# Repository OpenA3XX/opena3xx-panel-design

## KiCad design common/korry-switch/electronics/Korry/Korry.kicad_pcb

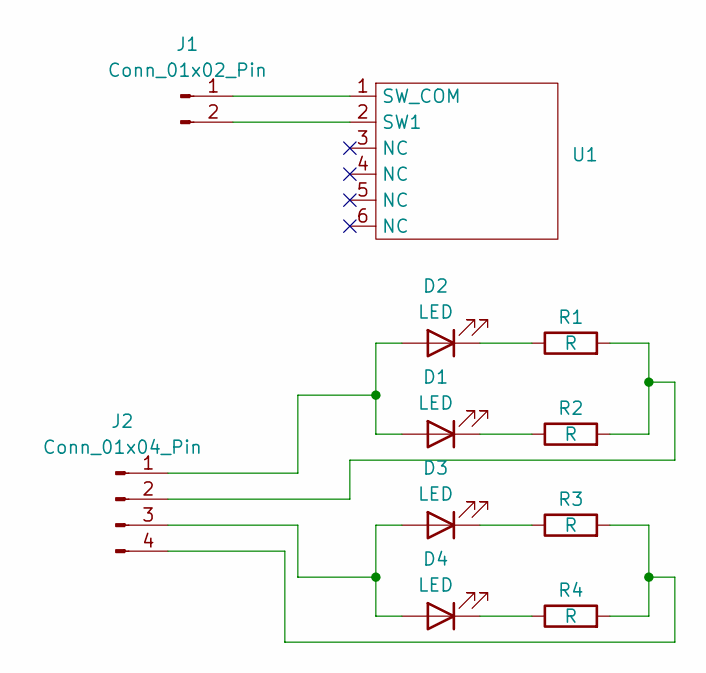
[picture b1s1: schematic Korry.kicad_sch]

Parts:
D1, D2, D3, D4: LED; LED_D3.0mm
J1: Conn_01x02_Pin; PinHeader_1x02_P2.54mm_Vertical
J2: Conn_01x04_Pin; PinHeader_1x04_P2.54mm_Vertical
R1, R2, R3, R4: R; R_1210_3225Metric_Pad1.30x2.65mm_HandSolder
U1: Korry_Switch_Discrete

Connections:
unnamed: D1.2 (A), D2.2 (A), J2.1
unnamed: D1.1 (K), R2.1
unnamed: D2.1 (K), R1.1
unnamed: D3.2 (A), D4.2 (A), J2.3
unnamed: D3.1 (K), R3.1
unnamed: D4.1 (K), R4.1
unnamed: J1.1, U1.1 (SW_COM)
unnamed: J1.2, U1.2 (SW1)
unnamed: J2.2, R1.2, R2.2
unnamed: J2.4, R3.2, R4.2

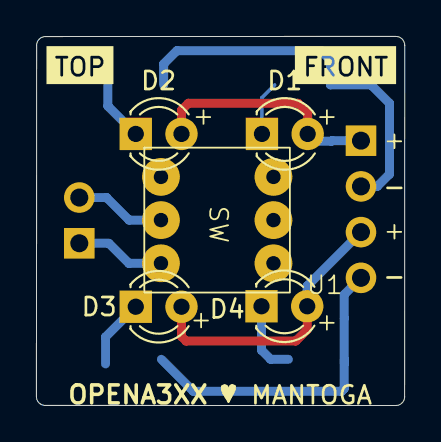
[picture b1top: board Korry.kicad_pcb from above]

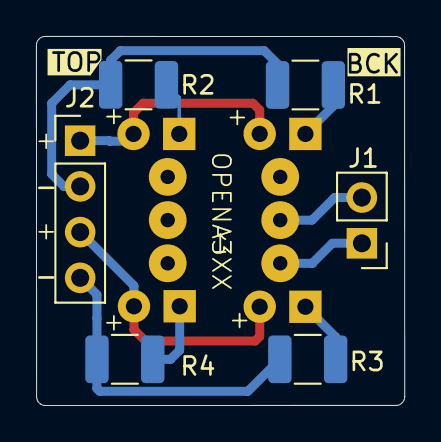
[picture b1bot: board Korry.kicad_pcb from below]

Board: 2 copper layers, 20.5 x 20.5 mm, 11 parts (6 on the bottom side), 10 nets.

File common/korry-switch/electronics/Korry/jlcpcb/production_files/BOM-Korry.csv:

Comment,Designator,Footprint,LCSC,Quantity
R,"R1,R2,R3,R4",R_1210_3225Metric_Pad1.30x2.65mm_HandSolder,C105021,4
LED,D2,LED_D3.0mm,,1
LED,D1,LED_D3.0mm,,1
Conn_01x04_Pin,J2,PinHeader_1x04_P2.54mm_Vertical,,1
LED,D4,LED_D3.0mm,,1
Conn_01x02_Pin,J1,PinHeader_1x02_P2.54mm_Vertical,,1
LED,D3,LED_D3.0mm,,1

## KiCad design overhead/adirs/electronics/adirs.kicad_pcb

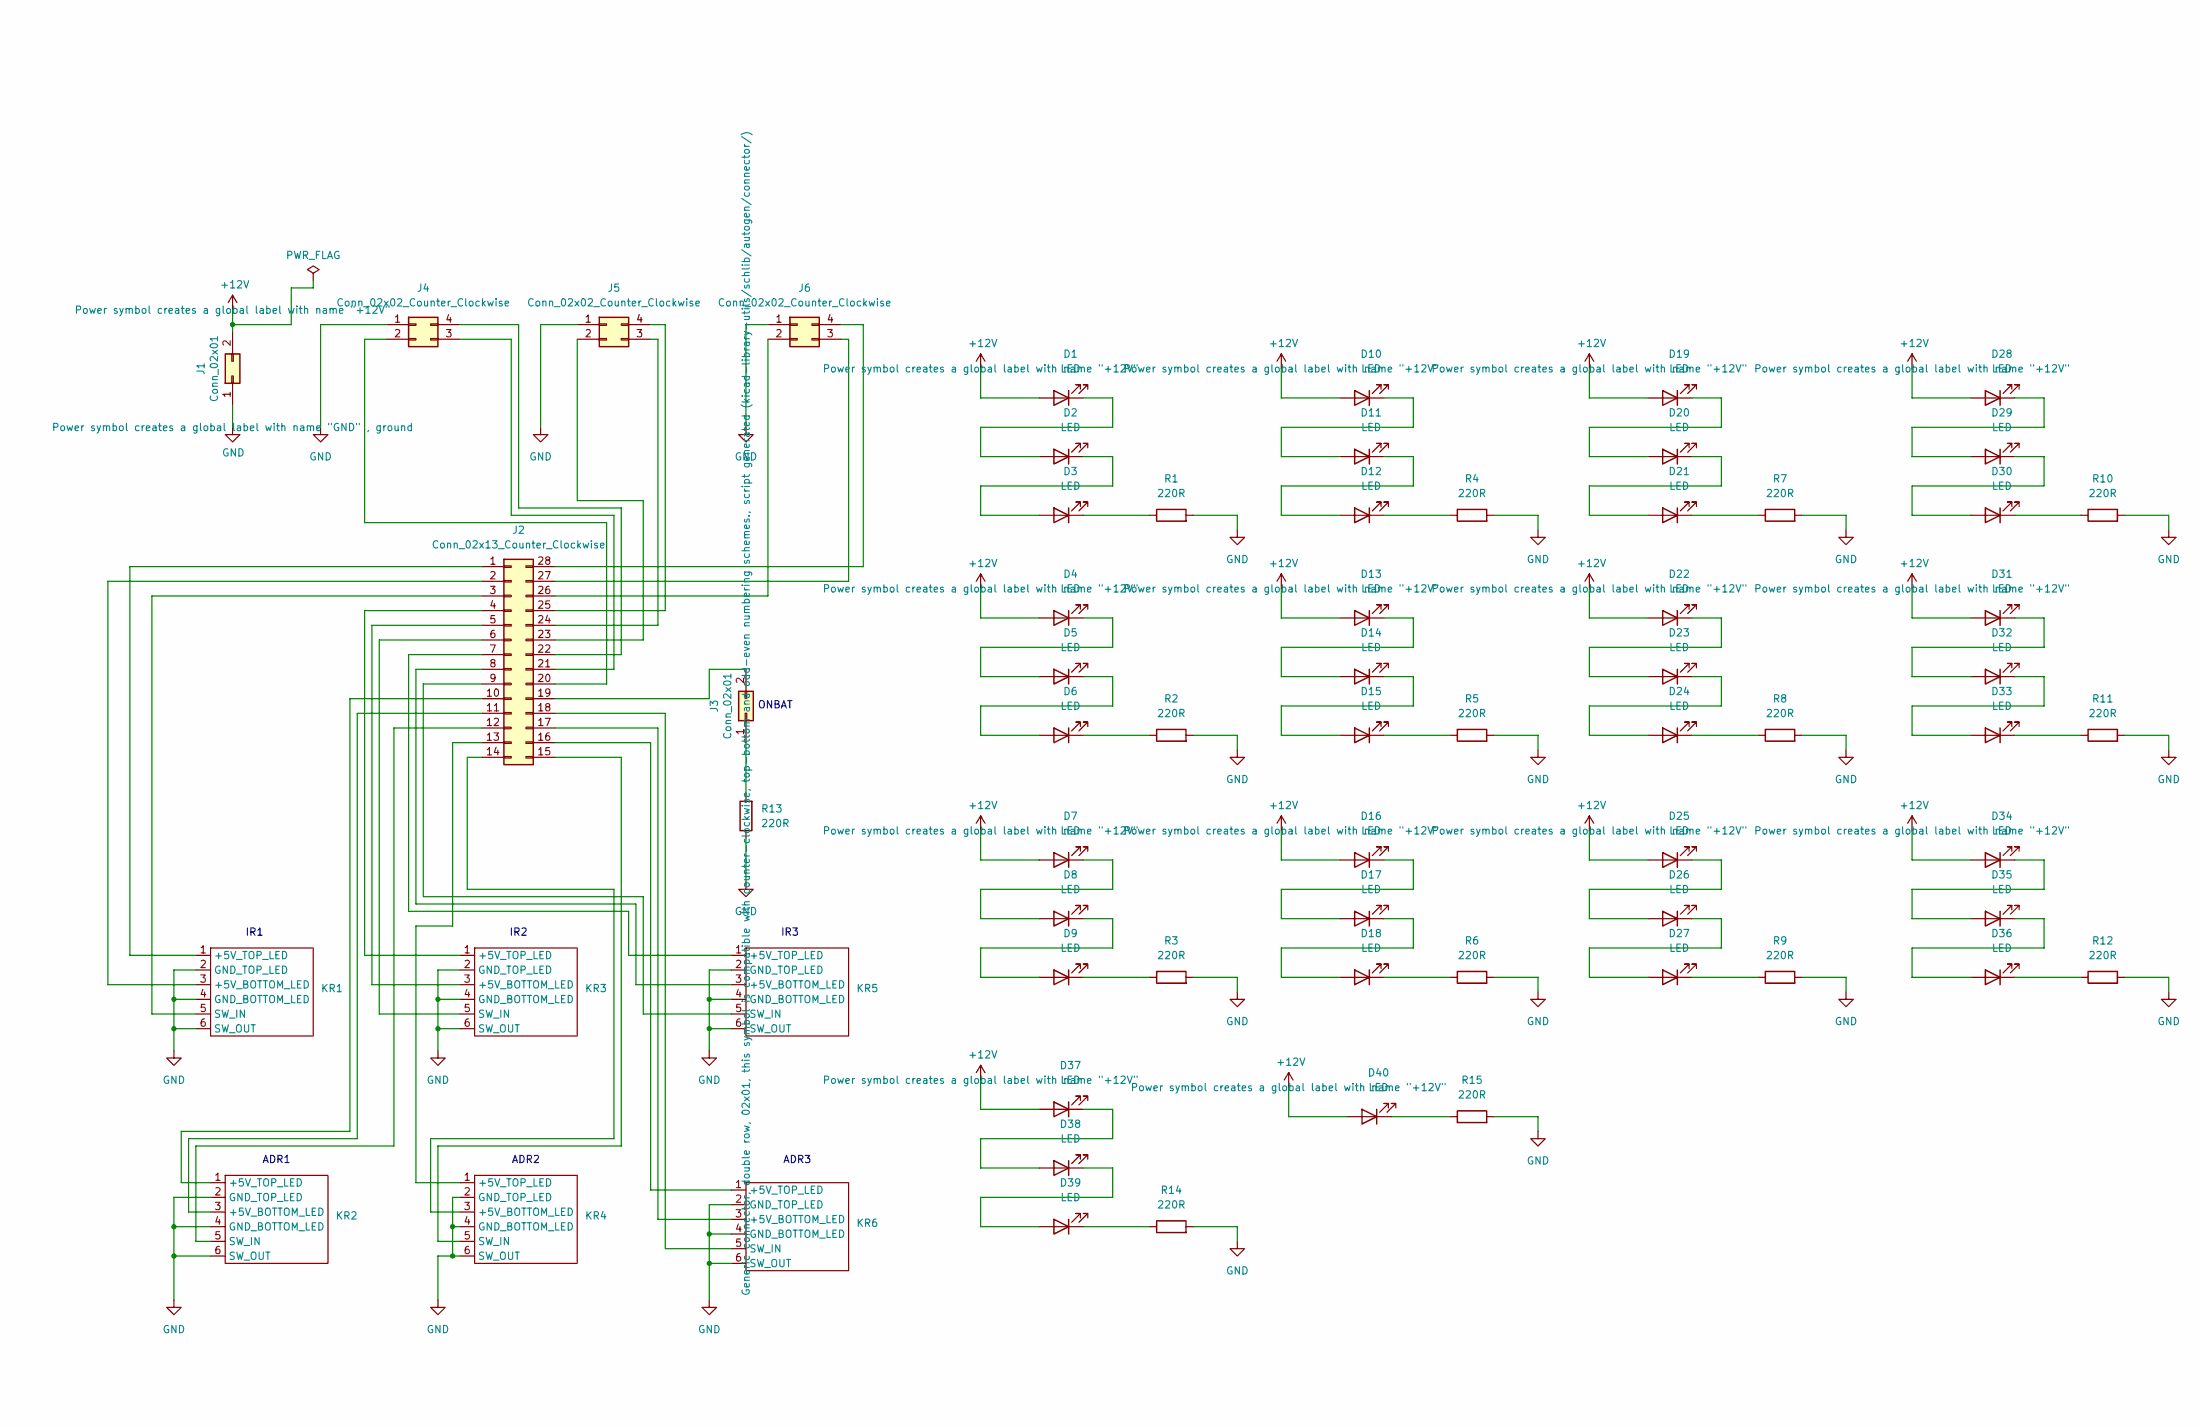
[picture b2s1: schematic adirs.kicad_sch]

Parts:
D1, D2, D3, D4, D5, D6, D7, D8, D9, D10, D11, D12, D13, D14, D15, D16, D17, D18, D19, D20, D21, D22, D23, D24, D25, D26, D27, D28, D29, D30, D31, D32, D33, D34, D35, D36, D37, D38, D39, D40: LED; LED_Everlight-SMD3528_3.5x2.8mm_67-21ST
J1: Conn_02x01; TerminalBlock_bornier-2_P5.08mm
J2: Conn_02x13_Counter_Clockwise; PinHeader_2x14_P2.54mm_Vertical
J3: Conn_02x01; PinHeader_1x02_P2.54mm_Vertical
J4, J5, J6: Conn_02x02_Counter_Clockwise; PinHeader_1x04_P2.54mm_Vertical
KR1, KR2, KR3, KR4, KR5, KR6: Korry Switch
R1, R2, R3, R4, R5, R6, R7, R8, R9, R10, R11, R12, R13, R14, R15: 220R; R_1206_3216Metric_Pad1.30x1.75mm_HandSolder

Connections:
+12V: D1.2 (A), D4.2 (A), D7.2 (A), D10.2 (A), D13.2 (A), D16.2 (A), D19.2 (A), D22.2 (A), D25.2 (A), D28.2 (A), D31.2 (A), D34.2 (A), D37.2 (A), D40.2 (A), J1.2
GND: J1.1, J4.1, J5.1, J6.1, KR1.2 (GND_TOP_LED), KR1.4 (GND_BOTTOM_LED), KR1.6 (SW_OUT), KR2.2 (GND_TOP_LED), KR2.4 (GND_BOTTOM_LED), KR2.6 (SW_OUT), KR3.2 (GND_TOP_LED), KR3.4 (GND_BOTTOM_LED), KR3.6 (SW_OUT), KR4.2 (GND_TOP_LED), KR4.4 (GND_BOTTOM_LED), KR4.6 (SW_OUT), KR5.2 (GND_TOP_LED), KR5.4 (GND_BOTTOM_LED), KR5.6 (SW_OUT), KR6.2 (GND_TOP_LED), KR6.4 (GND_BOTTOM_LED), KR6.6 (SW_OUT), R1.2, R2.2, R3.2, R4.2, R5.2, R6.2, R7.2, R8.2, R9.2, R10.2, R11.2, R12.2, R13.1, R14.2, R15.2
unnamed: D1.1 (K), D2.2 (A)
unnamed: D2.1 (K), D3.2 (A)
unnamed: D3.1 (K), R1.1
unnamed: D4.1 (K), D5.2 (A)
unnamed: D5.1 (K), D6.2 (A)
unnamed: D6.1 (K), R2.1
unnamed: D7.1 (K), D8.2 (A)
unnamed: D8.1 (K), D9.2 (A)
unnamed: D9.1 (K), R3.1
unnamed: D10.1 (K), D11.2 (A)
unnamed: D11.1 (K), D12.2 (A)
unnamed: D12.1 (K), R4.1
unnamed: D13.1 (K), D14.2 (A)
unnamed: D14.1 (K), D15.2 (A)
unnamed: D15.1 (K), R5.1
unnamed: D16.1 (K), D17.2 (A)
unnamed: D17.1 (K), D18.2 (A)
unnamed: D18.1 (K), R6.1
unnamed: D19.1 (K), D20.2 (A)
unnamed: D20.1 (K), D21.2 (A)
unnamed: D21.1 (K), R7.1
unnamed: D22.1 (K), D23.2 (A)
unnamed: D23.1 (K), D24.2 (A)
unnamed: D24.1 (K), R8.1
unnamed: D25.1 (K), D26.2 (A)
unnamed: D26.1 (K), D27.2 (A)
unnamed: D27.1 (K), R9.1
unnamed: D28.1 (K), D29.2 (A)
unnamed: D29.1 (K), D30.2 (A)
unnamed: D30.1 (K), R10.1
unnamed: D31.1 (K), D32.2 (A)
unnamed: D32.1 (K), D33.2 (A)
unnamed: D33.1 (K), R11.1
unnamed: D34.1 (K), D35.2 (A)
unnamed: D35.1 (K), D36.2 (A)
unnamed: D36.1 (K), R12.1
unnamed: D37.1 (K), D38.2 (A)
unnamed: D38.1 (K), D39.2 (A)
unnamed: D39.1 (K), R14.1
unnamed: D40.1 (K), R15.1
unnamed: J2.1, KR1.1 (+5V_TOP_LED)
unnamed: J2.2, KR1.3 (+5V_BOTTOM_LED)
unnamed: J2.3, KR1.5 (SW_IN)
unnamed: J2.4, KR3.1 (+5V_TOP_LED)
unnamed: J2.5, KR3.3 (+5V_BOTTOM_LED)
unnamed: J2.6, KR3.5 (SW_IN)
unnamed: J2.7, KR5.1 (+5V_TOP_LED)
unnamed: J2.8, KR5.3 (+5V_BOTTOM_LED)
unnamed: J2.9, KR5.5 (SW_IN)
unnamed: J2.10, KR2.1 (+5V_TOP_LED)
unnamed: J2.11, KR2.3 (+5V_BOTTOM_LED)
unnamed: J2.12, KR2.5 (SW_IN)
unnamed: J2.13, KR4.1 (+5V_TOP_LED)
unnamed: J2.14, KR4.3 (+5V_BOTTOM_LED)
unnamed: J2.15, KR4.5 (SW_IN)
unnamed: J2.16, KR6.1 (+5V_TOP_LED)
unnamed: J2.17, KR6.3 (+5V_BOTTOM_LED)
unnamed: J2.18, KR6.5 (SW_IN)
unnamed: J2.19, J3.2
unnamed: J2.20, J4.2
unnamed: J2.21, J4.3
unnamed: J2.22, J4.4
unnamed: J2.23, J5.2
unnamed: J2.24, J5.3
unnamed: J2.25, J5.4
unnamed: J2.26, J6.2
unnamed: J2.27, J6.3
unnamed: J2.28, J6.4
unnamed: J3.1, R13.2

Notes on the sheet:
IR1
IR2
ONBAT
IR3
ADR2
ADR3
ADR1

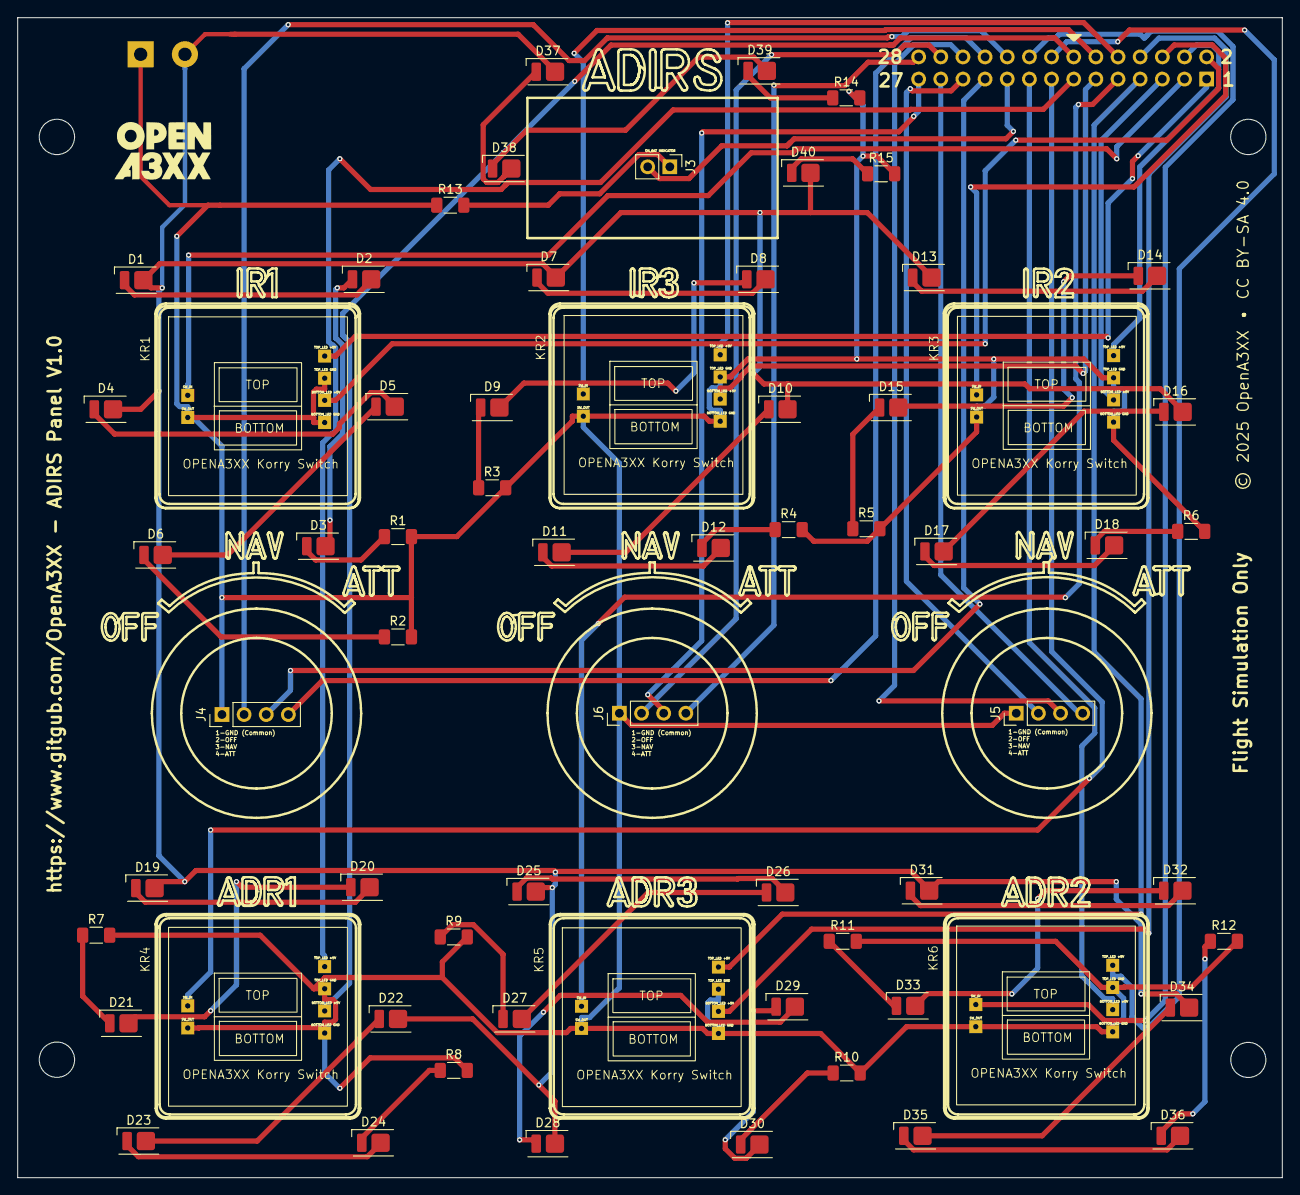
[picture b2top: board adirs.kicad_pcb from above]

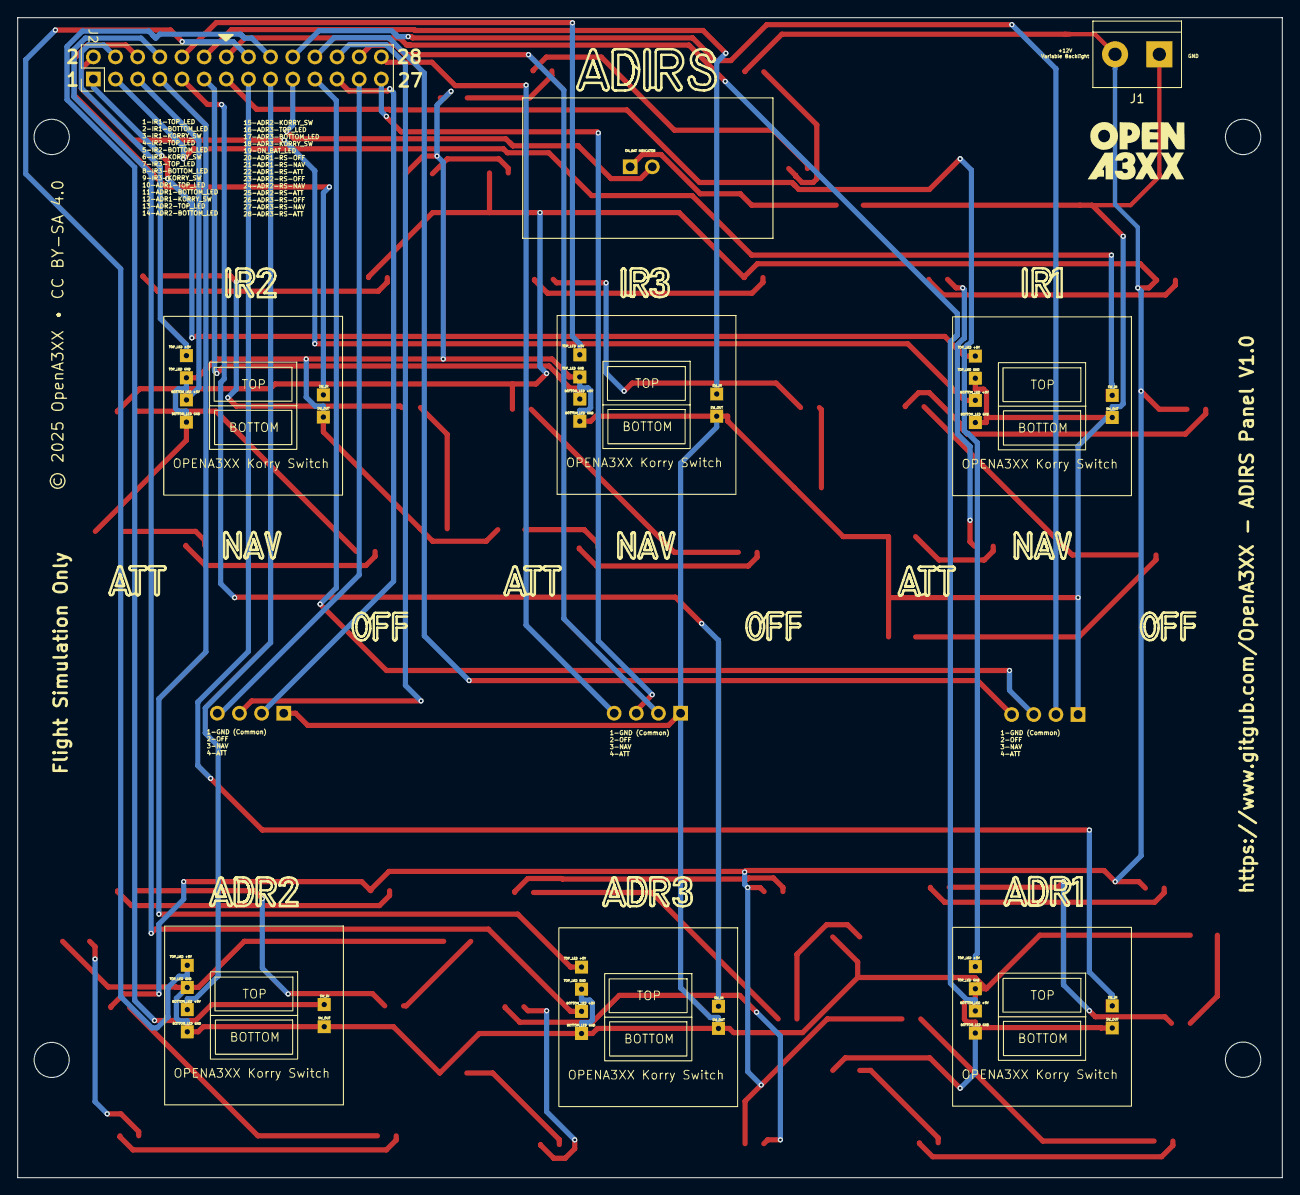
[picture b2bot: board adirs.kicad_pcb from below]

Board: 2 copper layers, 145.0 x 133.0 mm, 68 parts (3 on the bottom side), 71 nets.

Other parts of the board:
Bottom: LOGO; OpenA3XXLogoSmall

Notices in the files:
overhead/adirs/electronics/adirs.kicad_pcb:
© 2025 OpenA3XX • CC BY-SA 4.0
